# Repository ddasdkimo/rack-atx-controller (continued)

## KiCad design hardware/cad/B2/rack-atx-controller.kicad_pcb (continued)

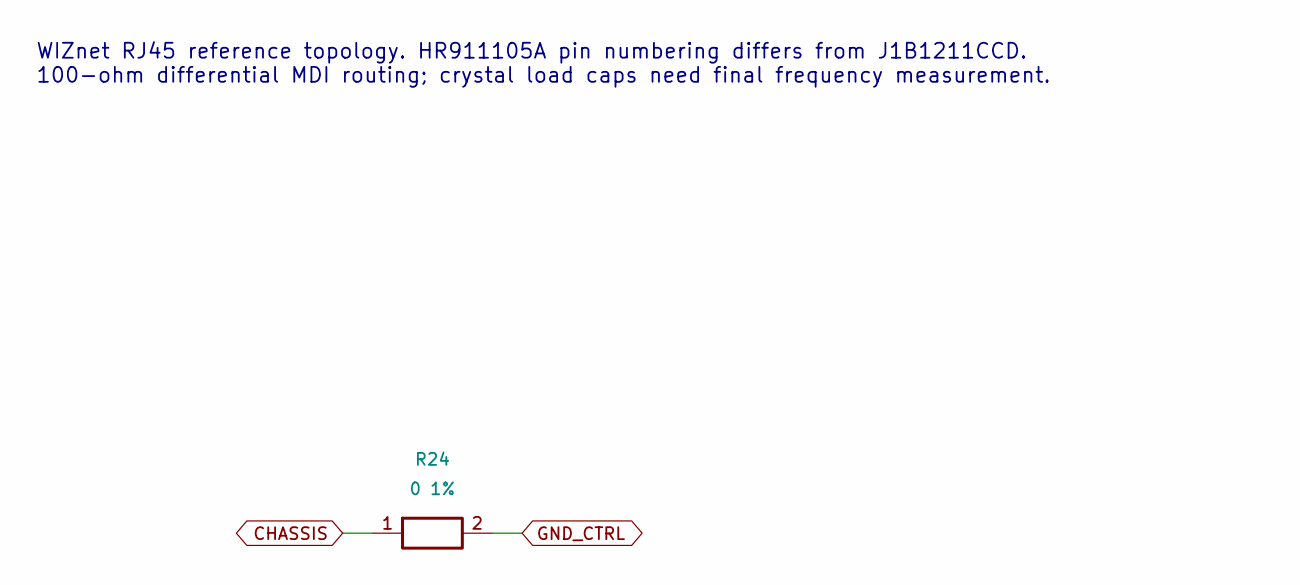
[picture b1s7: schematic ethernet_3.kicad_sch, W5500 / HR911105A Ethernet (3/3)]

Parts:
R24: 0 1%; R_0603_1608Metric; MPN 0603WAF0000T5E; LCSC C21189

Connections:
CHASSIS: R24.1; also elsewhere on the board
GND_CTRL: R24.2; also elsewhere on the board

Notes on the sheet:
WIZnet RJ45 reference topology. HR911105A pin numbering differs from J1B1211CCD. 100-ohm differential MDI routing; crystal load caps need final frequency measurement.

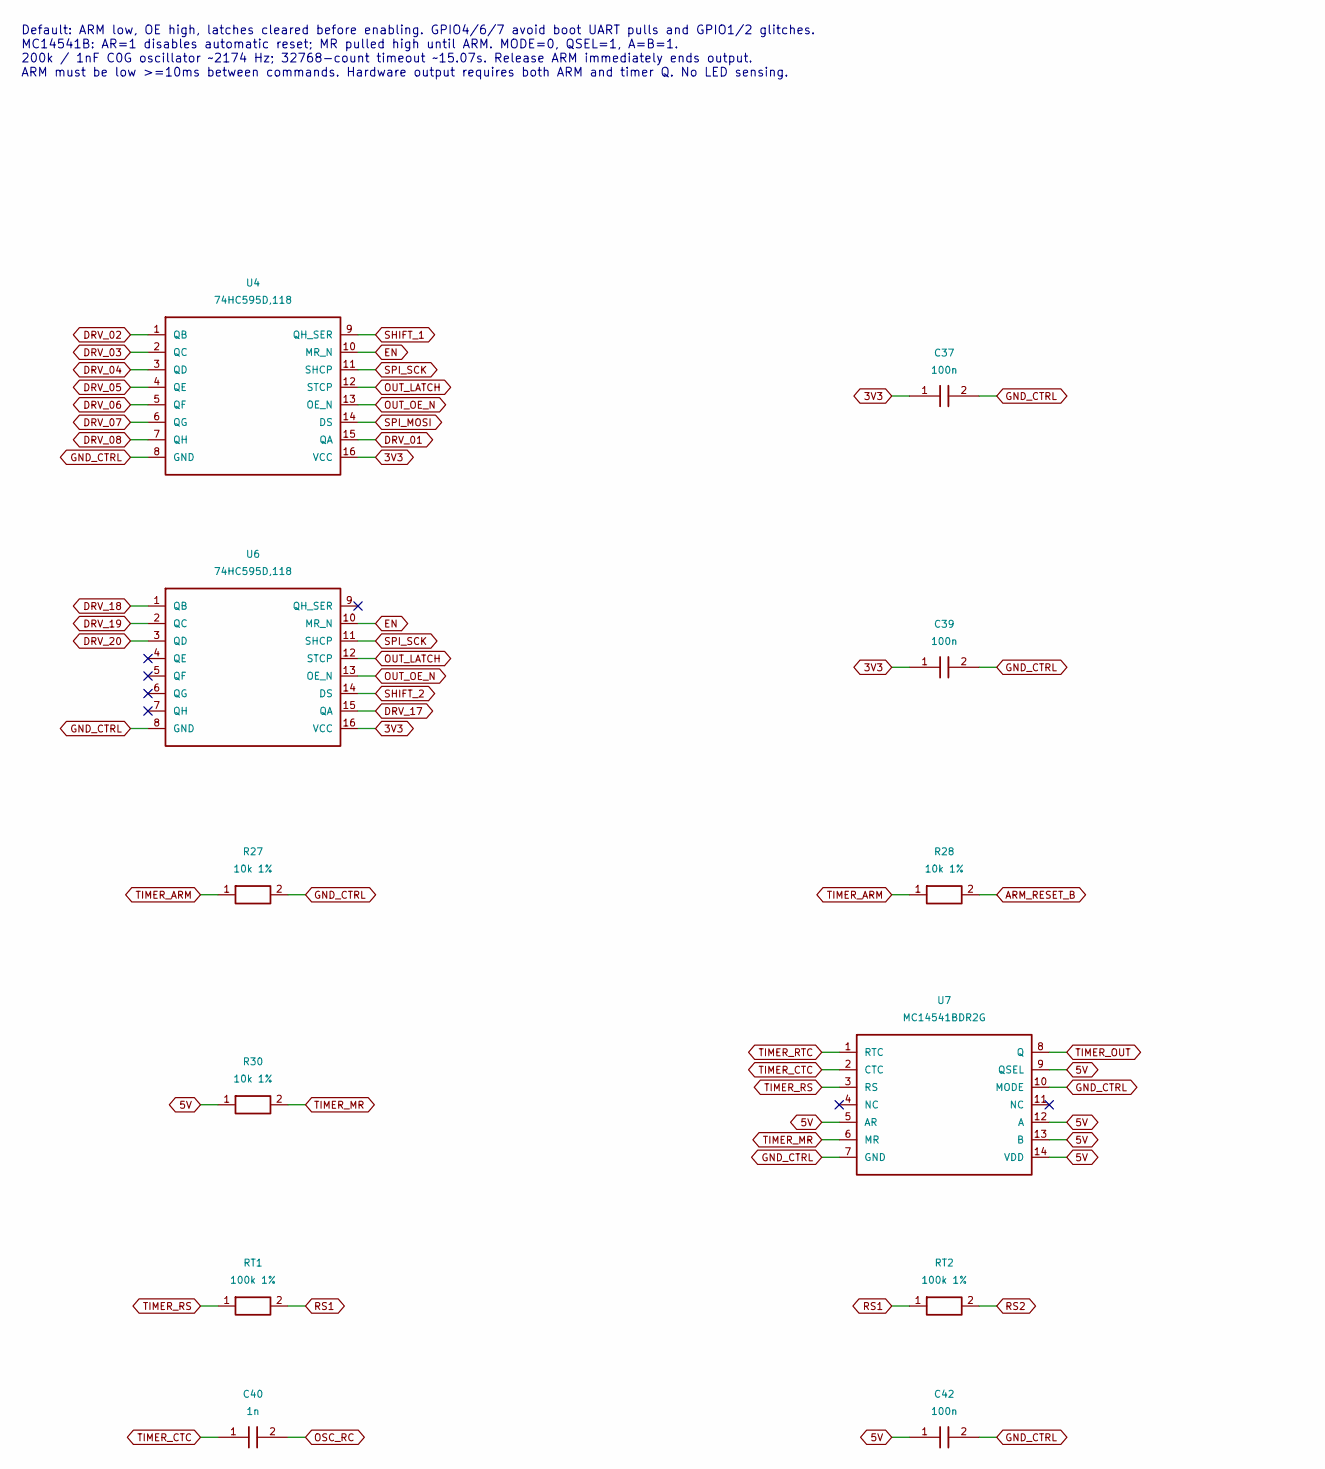
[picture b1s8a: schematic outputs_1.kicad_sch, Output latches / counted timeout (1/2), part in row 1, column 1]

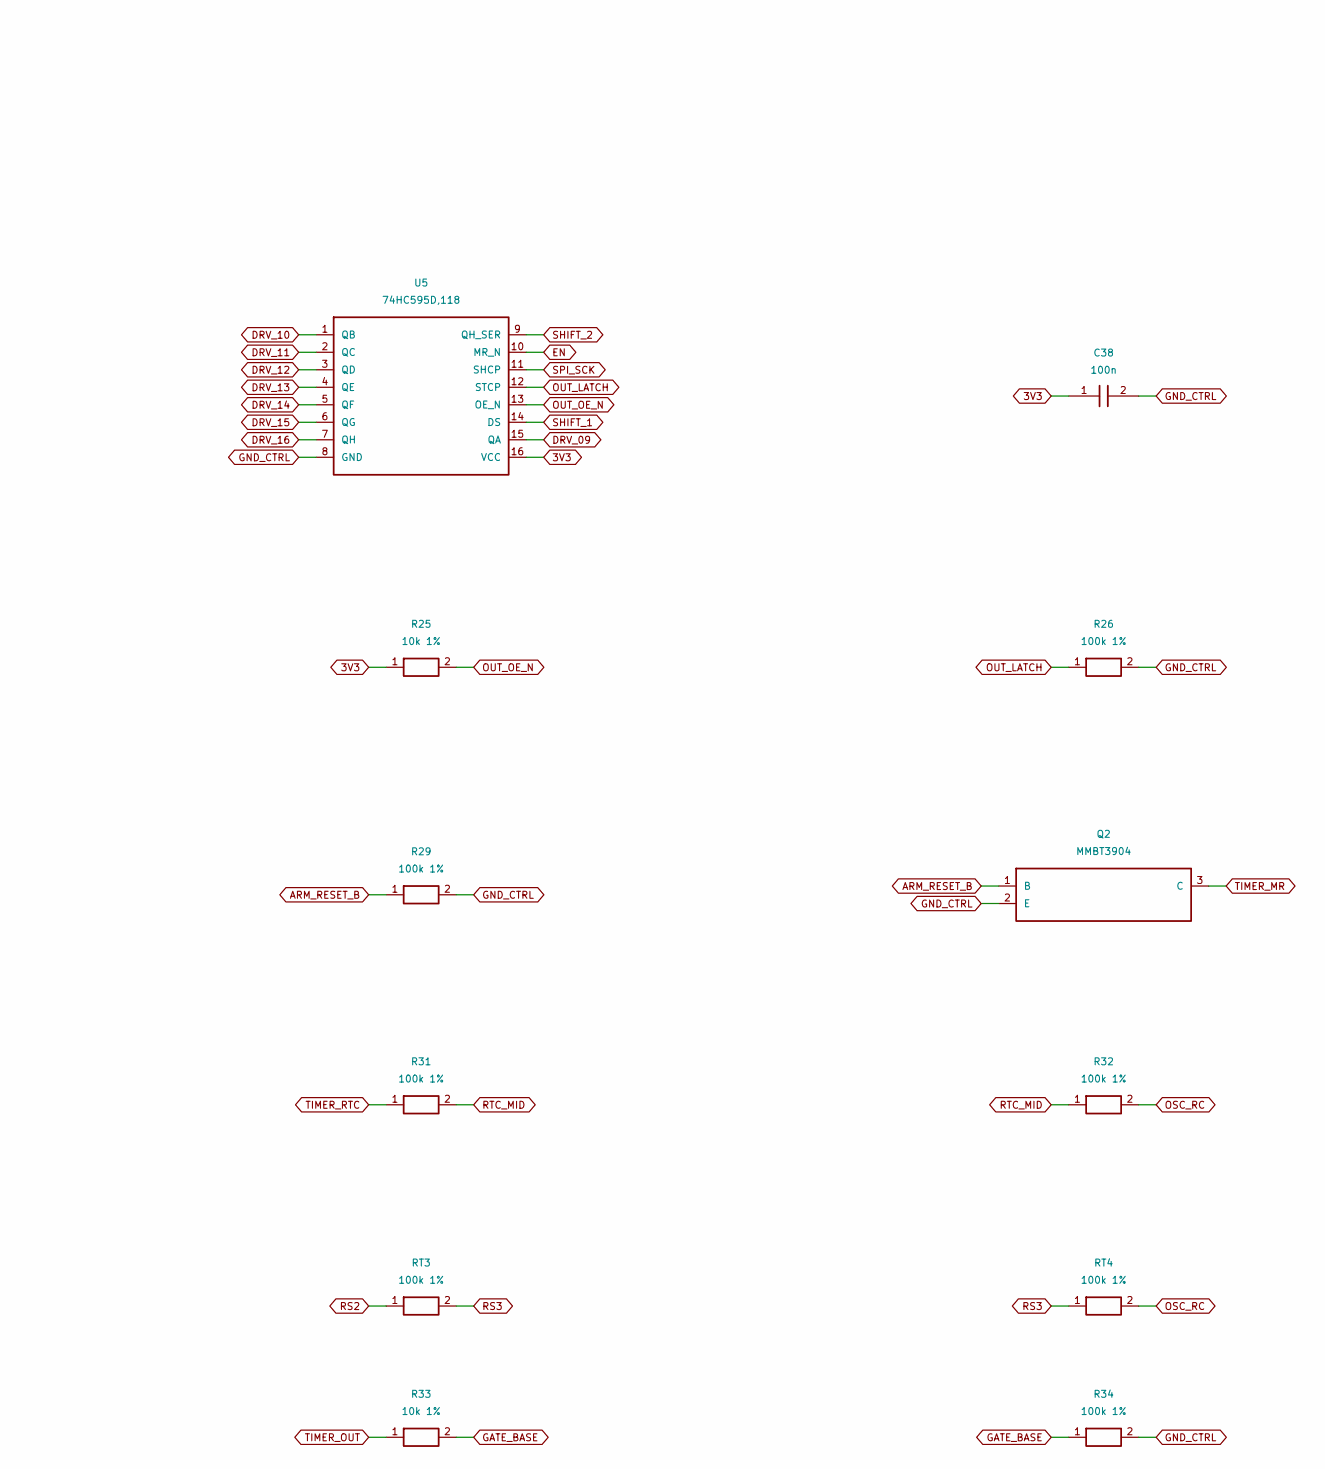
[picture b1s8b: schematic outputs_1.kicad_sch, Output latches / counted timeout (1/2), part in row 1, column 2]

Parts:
C37, C38, C39, C42: 100n; C_0603_1608Metric; MPN CC0603KRX7R9BB104; LCSC C14663
C40: 1n; C_0603_1608Metric; MPN CL10C102JB8NNNC; LCSC C163508
Q2: MMBT3904; SOT-23; MPN MMBT3904(RANGE:100-300); LCSC C20526
R25, R27, R28, R30, R33: 10k 1%; R_0603_1608Metric; MPN 0603WAF1002T5E; LCSC C25804
R26, R29, R31, R32, R34: 100k 1%; R_0603_1608Metric; MPN 0603WAF1003T5E; LCSC C25803
RT1, RT2, RT3, RT4: 100k 1%; R_0603_1608Metric; MPN 0603WAF1003T5E; LCSC C25803
U4, U5, U6: 74HC595D,118; SOIC-16_3.9x9.9mm_P1.27mm; MPN 74HC595D,118; LCSC C5947
U7: MC14541BDR2G; SOIC-14_3.9x8.7mm_P1.27mm; MPN MC14541BDR2G; LCSC C7292

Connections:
3V3: C37.1, C38.1, C39.1, R25.1, U4.16 (VCC), U5.16 (VCC), U6.16 (VCC); also elsewhere on the board
5V: C42.1, R30.1, U7.5 (AR), U7.9 (QSEL), U7.12 (A), U7.13 (B), U7.14 (VDD); also elsewhere on the board
ARM_RESET_B: Q2.1 (B), R28.2, R29.1
DRV_01: U4.15 (QA); also elsewhere on the board
DRV_02: U4.1 (QB); also elsewhere on the board
DRV_03: U4.2 (QC); also elsewhere on the board
DRV_04: U4.3 (QD); also elsewhere on the board
DRV_05: U4.4 (QE); also elsewhere on the board
DRV_06: U4.5 (QF); also elsewhere on the board
DRV_07: U4.6 (QG); also elsewhere on the board
DRV_08: U4.7 (QH); also elsewhere on the board
DRV_09: U5.15 (QA); also elsewhere on the board
DRV_10: U5.1 (QB); also elsewhere on the board
DRV_11: U5.2 (QC); also elsewhere on the board
DRV_12: U5.3 (QD); also elsewhere on the board
DRV_13: U5.4 (QE); also elsewhere on the board
DRV_14: U5.5 (QF); also elsewhere on the board
DRV_15: U5.6 (QG); also elsewhere on the board
DRV_16: U5.7 (QH); also elsewhere on the board
DRV_17: U6.15 (QA); also elsewhere on the board
DRV_18: U6.1 (QB); also elsewhere on the board
DRV_19: U6.2 (QC); also elsewhere on the board
DRV_20: U6.3 (QD); also elsewhere on the board
EN: U4.10 (MR_N), U5.10 (MR_N), U6.10 (MR_N); also elsewhere on the board
GATE_BASE: R33.2, R34.1; also elsewhere on the board
GND_CTRL: C37.2, C38.2, C39.2, C42.2, Q2.2 (E), R26.2, R27.2, R29.2, R34.2, U4.8 (GND), U5.8 (GND), U6.8 (GND), U7.7 (GND), U7.10 (MODE); also elsewhere on the board
OSC_RC: C40.2, R32.2, RT4.2
OUT_LATCH: R26.1, U4.12 (STCP), U5.12 (STCP), U6.12 (STCP); also elsewhere on the board
OUT_OE_N: R25.2, U4.13 (OE_N), U5.13 (OE_N), U6.13 (OE_N); also elsewhere on the board
RS1: RT1.2, RT2.1
RS2: RT2.2, RT3.1
RS3: RT3.2, RT4.1
RTC_MID: R31.2, R32.1
SHIFT_1: U4.9 (QH_SER), U5.14 (DS)
SHIFT_2: U5.9 (QH_SER), U6.14 (DS)
SPI_MOSI: U4.14 (DS); also elsewhere on the board
SPI_SCK: U4.11 (SHCP), U5.11 (SHCP), U6.11 (SHCP); also elsewhere on the board
TIMER_ARM: R27.1, R28.1; also elsewhere on the board
TIMER_CTC: C40.1, U7.2 (CTC)
TIMER_MR: Q2.3 (C), R30.2, U7.6 (MR)
TIMER_OUT: R33.1, U7.8 (Q)
TIMER_RS: RT1.1, U7.3 (RS)
TIMER_RTC: R31.1, U7.1 (RTC)

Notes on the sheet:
Default: ARM low, OE high, latches cleared before enabling. GPIO4/6/7 avoid boot UART pulls and GPIO1/2 glitches. MC14541B: AR=1 disables automatic reset; MR pulled high until ARM. MODE=0, QSEL=1, A=B=1. 200k / 1nF C0G oscillator ~2174 Hz; 32768-count timeout ~15.07s. Release ARM immediately ends o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

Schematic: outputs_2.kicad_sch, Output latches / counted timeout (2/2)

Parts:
Q3, Q200: MMBT3904; SOT-23; MPN MMBT3904(RANGE:100-300); LCSC C20526
Q4: AO3401A; SOT-23; MPN AO3401A; LCSC C15127
R35, R36, R37: 10k 1%; R_0603_1608Metric; MPN 0603WAF1002T5E; LCSC C25804
R38: 100k 1%; R_0603_1608Metric; MPN 0603WAF1003T5E; LCSC C25803

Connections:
5V: Q4.2 (S), R35.2; also elsewhere on the board
ARM_GATE_B: Q200.1 (B), R37.2, R38.1
ARM_SINK: Q3.2 (E), Q200.3 (C)
GATE_BASE: Q3.1 (B); also elsewhere on the board
GND_CTRL: Q200.2 (E), R36.2, R38.2; also elsewhere on the board
PHOTO_5V: Q4.3 (D), R36.1; also elsewhere on the board
PHOTO_GATE: Q3.3 (C), Q4.1 (G), R35.1
TIMER_ARM: R37.1; also elsewhere on the board

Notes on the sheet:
Default: ARM low, OE high, latches cleared before enabling. GPIO4/6/7 avoid boot UART pulls and GPIO1/2 glitches. MC14541B: AR=1 disables automatic reset; MR pulled high until ARM. MODE=0, QSEL=1, A=B=1. 200k / 1nF C0G oscillator ~2174 Hz; 32768-count timeout ~15.07s. Release ARM immediately ends o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

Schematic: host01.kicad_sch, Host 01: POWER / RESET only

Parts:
D2, D3: PESD5V0S2BT; SOT-23; MPN PESD5V0S2BT; LCSC C2841440
D101, D102: KT-0603R / RED; LED_0603_1608Metric_CathodeSilk; MPN KT-0603R; LCSC C2286
J01: S10B-PHDSS(LF)(SN); JST_PHD_S10B-PHDSS_2x05_P2.00mm_Horizontal; MPN S10B-PHDSS(LF)(SN); LCSC C161672
Q5, Q6: MMBT3904; SOT-23; MPN MMBT3904(RANGE:100-300); LCSC C20526
R39, R43, R301, R302: 1.5k 1%; R_0603_1608Metric; MPN 0603WAF1501T5E; LCSC C22843
R40, R44: 100k 1%; R_0603_1608Metric; MPN 0603WAF1003T5E; LCSC C25803
R41, R42, R45, R46: 220 1%; R_0603_1608Metric; MPN 0603WAF2200T5E; LCSC C22962
U8, U9: TLP3122A(TPL,E; TLP3122A_11-4M1S; MPN TLP3122A(TPL,E; LCSC C4153843

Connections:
CTRL_H01_PWR_A: R42.2, U8.1 (A)
CTRL_H01_PWR_B: Q5.1 (B), R39.2, R40.1
CTRL_H01_PWR_IND_A: D101.2 (A), R301.2
CTRL_H01_PWR_K: D101.1 (K), Q5.3 (C), U8.3 (K)
CTRL_H01_PWR_R: R41.2, R42.1
CTRL_H01_RST_A: R46.2, U9.1 (A)
CTRL_H01_RST_B: Q6.1 (B), R43.2, R44.1
CTRL_H01_RST_IND_A: D102.2 (A), R302.2
CTRL_H01_RST_K: D102.1 (K), Q6.3 (C), U9.3 (K)
CTRL_H01_RST_R: R45.2, R46.1
DRV_01: R39.1; also elsewhere on the board
DRV_02: R43.1; also elsewhere on the board
GND_CTRL: Q5.2 (E), Q6.2 (E), R40.2, R44.2; also elsewhere on the board
H01_GND: D2.3 (GND), D3.3 (GND), J01.9 (HOST_REF)
H01_PWR_A: D2.1 (IO1), J01.1 (PWR_A), U8.4 (OUT)
H01_PWR_B: D2.2 (IO2), J01.2 (PWR_B), U8.6 (OUT)
H01_RST_A: D3.1 (IO1), J01.3 (RST_A), U9.4 (OUT)
H01_RST_B: D3.2 (IO2), J01.4 (RST_B), U9.6 (OUT)
PHOTO_5V: R41.1, R45.1, R301.1, R302.1; also elsewhere on the board

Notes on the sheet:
Two isolated normally-open contacts parallel the original case buttons. No host LED sensing or isolated supply. Pin 9 remains this host reference for button ESD protection ONLY. Do not join host references to controller ground or to one another. Pins 5..8 and 10 are NC. Use verified motherboard sig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

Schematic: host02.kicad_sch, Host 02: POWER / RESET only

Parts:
D4, D5: PESD5V0S2BT; SOT-23; MPN PESD5V0S2BT; LCSC C2841440
D103, D104: KT-0603R / RED; LED_0603_1608Metric_CathodeSilk; MPN KT-0603R; LCSC C2286
J02: S10B-PHDSS(LF)(SN); JST_PHD_S10B-PHDSS_2x05_P2.00mm_Horizontal; MPN S10B-PHDSS(LF)(SN); LCSC C161672
Q7, Q8: MMBT3904; SOT-23; MPN MMBT3904(RANGE:100-300); LCSC C20526
R47, R51, R303, R304: 1.5k 1%; R_0603_1608Metric; MPN 0603WAF1501T5E; LCSC C22843
R48, R52: 100k 1%; R_0603_1608Metric; MPN 0603WAF1003T5E; LCSC C25803
R49, R50, R53, R54: 220 1%; R_0603_1608Metric; MPN 0603WAF2200T5E; LCSC C22962
U10, U11: TLP3122A(TPL,E; TLP3122A_11-4M1S; MPN TLP3122A(TPL,E; LCSC C4153843

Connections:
CTRL_H02_PWR_A: R50.2, U10.1 (A)
CTRL_H02_PWR_B: Q7.1 (B), R47.2, R48.1
CTRL_H02_PWR_IND_A: D103.2 (A), R303.2
CTRL_H02_PWR_K: D103.1 (K), Q7.3 (C), U10.3 (K)
CTRL_H02_PWR_R: R49.2, R50.1
CTRL_H02_RST_A: R54.2, U11.1 (A)
CTRL_H02_RST_B: Q8.1 (B), R51.2, R52.1
CTRL_H02_RST_IND_A: D104.2 (A), R304.2
CTRL_H02_RST_K: D104.1 (K), Q8.3 (C), U11.3 (K)
CTRL_H02_RST_R: R53.2, R54.1
DRV_03: R47.1; also elsewhere on the board
DRV_04: R51.1; also elsewhere on the board
GND_CTRL: Q7.2 (E), Q8.2 (E), R48.2, R52.2; also elsewhere on the board
H02_GND: D4.3 (GND), D5.3 (GND), J02.9 (HOST_REF)
H02_PWR_A: D4.1 (IO1), J02.1 (PWR_A), U10.4 (OUT)
H02_PWR_B: D4.2 (IO2), J02.2 (PWR_B), U10.6 (OUT)
H02_RST_A: D5.1 (IO1), J02.3 (RST_A), U11.4 (OUT)
H02_RST_B: D5.2 (IO2), J02.4 (RST_B), U11.6 (OUT)
PHOTO_5V: R49.1, R53.1, R303.1, R304.1; also elsewhere on the board

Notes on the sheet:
Two isolated normally-open contacts parallel the original case buttons. No host LED sensing or isolated supply. Pin 9 remains this host reference for button ESD protection ONLY. Do not join host references to controller ground or to one another. Pins 5..8 and 10 are NC. Use verified motherboard sig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

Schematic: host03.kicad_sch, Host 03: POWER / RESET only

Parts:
D6, D7: PESD5V0S2BT; SOT-23; MPN PESD5V0S2BT; LCSC C2841440
D105, D106: KT-0603R / RED; LED_0603_1608Metric_CathodeSilk; MPN KT-0603R; LCSC C2286
J03: S10B-PHDSS(LF)(SN); JST_PHD_S10B-PHDSS_2x05_P2.00mm_Horizontal; MPN S10B-PHDSS(LF)(SN); LCSC C161672
Q9, Q10: MMBT3904; SOT-23; MPN MMBT3904(RANGE:100-300); LCSC C20526
R55, R59, R305, R306: 1.5k 1%; R_0603_1608Metric; MPN 0603WAF1501T5E; LCSC C22843
R56, R60: 100k 1%; R_0603_1608Metric; MPN 0603WAF1003T5E; LCSC C25803
R57, R58, R61, R62: 220 1%; R_0603_1608Metric; MPN 0603WAF2200T5E; LCSC C22962
U12, U13: TLP3122A(TPL,E; TLP3122A_11-4M1S; MPN TLP3122A(TPL,E; LCSC C4153843

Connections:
CTRL_H03_PWR_A: R58.2, U12.1 (A)
CTRL_H03_PWR_B: Q9.1 (B), R55.2, R56.1
CTRL_H03_PWR_IND_A: D105.2 (A), R305.2
CTRL_H03_PWR_K: D105.1 (K), Q9.3 (C), U12.3 (K)
CTRL_H03_PWR_R: R57.2, R58.1
CTRL_H03_RST_A: R62.2, U13.1 (A)
CTRL_H03_RST_B: Q10.1 (B), R59.2, R60.1
CTRL_H03_RST_IND_A: D106.2 (A), R306.2
CTRL_H03_RST_K: D106.1 (K), Q10.3 (C), U13.3 (K)
CTRL_H03_RST_R: R61.2, R62.1
DRV_05: R55.1; also elsewhere on the board
DRV_06: R59.1; also elsewhere on the board
GND_CTRL: Q9.2 (E), Q10.2 (E), R56.2, R60.2; also elsewhere on the board
H03_GND: D6.3 (GND), D7.3 (GND), J03.9 (HOST_REF)
H03_PWR_A: D6.1 (IO1), J03.1 (PWR_A), U12.4 (OUT)
H03_PWR_B: D6.2 (IO2), J03.2 (PWR_B), U12.6 (OUT)
H03_RST_A: D7.1 (IO1), J03.3 (RST_A), U13.4 (OUT)
H03_RST_B: D7.2 (IO2), J03.4 (RST_B), U13.6 (OUT)
PHOTO_5V: R57.1, R61.1, R305.1, R306.1; also elsewhere on the board

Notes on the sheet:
Two isolated normally-open contacts parallel the original case buttons. No host LED sensing or isolated supply. Pin 9 remains this host reference for button ESD protection ONLY. Do not join host references to controller ground or to one another. Pins 5..8 and 10 are NC. Use verified motherboard sig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

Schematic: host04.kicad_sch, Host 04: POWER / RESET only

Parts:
D8, D9: PESD5V0S2BT; SOT-23; MPN PESD5V0S2BT; LCSC C2841440
D107, D108: KT-0603R / RED; LED_0603_1608Metric_CathodeSilk; MPN KT-0603R; LCSC C2286
J04: S10B-PHDSS(LF)(SN); JST_PHD_S10B-PHDSS_2x05_P2.00mm_Horizontal; MPN S10B-PHDSS(LF)(SN); LCSC C161672
Q11, Q12: MMBT3904; SOT-23; MPN MMBT3904(RANGE:100-300); LCSC C20526
R63, R67, R307, R308: 1.5k 1%; R_0603_1608Metric; MPN 0603WAF1501T5E; LCSC C22843
R64, R68: 100k 1%; R_0603_1608Metric; MPN 0603WAF1003T5E; LCSC C25803
R65, R66, R69, R70: 220 1%; R_0603_1608Metric; MPN 0603WAF2200T5E; LCSC C22962
U14, U15: TLP3122A(TPL,E; TLP3122A_11-4M1S; MPN TLP3122A(TPL,E; LCSC C4153843

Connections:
CTRL_H04_PWR_A: R66.2, U14.1 (A)
CTRL_H04_PWR_B: Q11.1 (B), R63.2, R64.1
CTRL_H04_PWR_IND_A: D107.2 (A), R307.2
CTRL_H04_PWR_K: D107.1 (K), Q11.3 (C), U14.3 (K)
CTRL_H04_PWR_R: R65.2, R66.1
CTRL_H04_RST_A: R70.2, U15.1 (A)
CTRL_H04_RST_B: Q12.1 (B), R67.2, R68.1
CTRL_H04_RST_IND_A: D108.2 (A), R308.2
CTRL_H04_RST_K: D108.1 (K), Q12.3 (C), U15.3 (K)
CTRL_H04_RST_R: R69.2, R70.1
DRV_07: R63.1; also elsewhere on the board
DRV_08: R67.1; also elsewhere on the board
GND_CTRL: Q11.2 (E), Q12.2 (E), R64.2, R68.2; also elsewhere on the board
H04_GND: D8.3 (GND), D9.3 (GND), J04.9 (HOST_REF)
H04_PWR_A: D8.1 (IO1), J04.1 (PWR_A), U14.4 (OUT)
H04_PWR_B: D8.2 (IO2), J04.2 (PWR_B), U14.6 (OUT)
H04_RST_A: D9.1 (IO1), J04.3 (RST_A), U15.4 (OUT)
H04_RST_B: D9.2 (IO2), J04.4 (RST_B), U15.6 (OUT)
PHOTO_5V: R65.1, R69.1, R307.1, R308.1; also elsewhere on the board

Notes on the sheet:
Two isolated normally-open contacts parallel the original case buttons. No host LED sensing or isolated supply. Pin 9 remains this host reference for button ESD protection ONLY. Do not join host references to controller ground or to one another. Pins 5..8 and 10 are NC. Use verified motherboard sig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

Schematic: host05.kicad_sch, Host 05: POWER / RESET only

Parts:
D10, D11: PESD5V0S2BT; SOT-23; MPN PESD5V0S2BT; LCSC C2841440
D109, D110: KT-0603R / RED; LED_0603_1608Metric_CathodeSilk; MPN KT-0603R; LCSC C2286
J05: S10B-PHDSS(LF)(SN); JST_PHD_S10B-PHDSS_2x05_P2.00mm_Horizontal; MPN S10B-PHDSS(LF)(SN); LCSC C161672
Q13, Q14: MMBT3904; SOT-23; MPN MMBT3904(RANGE:100-300); LCSC C20526
R71, R75, R309, R310: 1.5k 1%; R_0603_1608Metric; MPN 0603WAF1501T5E; LCSC C22843
R72, R76: 100k 1%; R_0603_1608Metric; MPN 0603WAF1003T5E; LCSC C25803
R73, R74, R77, R78: 220 1%; R_0603_1608Metric; MPN 0603WAF2200T5E; LCSC C22962
U16, U17: TLP3122A(TPL,E; TLP3122A_11-4M1S; MPN TLP3122A(TPL,E; LCSC C4153843

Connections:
CTRL_H05_PWR_A: R74.2, U16.1 (A)
CTRL_H05_PWR_B: Q13.1 (B), R71.2, R72.1
CTRL_H05_PWR_IND_A: D109.2 (A), R309.2
CTRL_H05_PWR_K: D109.1 (K), Q13.3 (C), U16.3 (K)
CTRL_H05_PWR_R: R73.2, R74.1
CTRL_H05_RST_A: R78.2, U17.1 (A)
CTRL_H05_RST_B: Q14.1 (B), R75.2, R76.1
CTRL_H05_RST_IND_A: D110.2 (A), R310.2
CTRL_H05_RST_K: D110.1 (K), Q14.3 (C), U17.3 (K)
CTRL_H05_RST_R: R77.2, R78.1
DRV_09: R71.1; also elsewhere on the board
DRV_10: R75.1; also elsewhere on the board
GND_CTRL: Q13.2 (E), Q14.2 (E), R72.2, R76.2; also elsewhere on the board
H05_GND: D10.3 (GND), D11.3 (GND), J05.9 (HOST_REF)
H05_PWR_A: D10.1 (IO1), J05.1 (PWR_A), U16.4 (OUT)
H05_PWR_B: D10.2 (IO2), J05.2 (PWR_B), U16.6 (OUT)
H05_RST_A: D11.1 (IO1), J05.3 (RST_A), U17.4 (OUT)
H05_RST_B: D11.2 (IO2), J05.4 (RST_B), U17.6 (OUT)
PHOTO_5V: R73.1, R77.1, R309.1, R310.1; also elsewhere on the board

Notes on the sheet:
Two isolated normally-open contacts parallel the original case buttons. No host LED sensing or isolated supply. Pin 9 remains this host reference for button ESD protection ONLY. Do not join host references to controller ground or to one another. Pins 5..8 and 10 are NC. Use verified motherboard sig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

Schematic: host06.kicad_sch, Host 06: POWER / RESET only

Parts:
D12, D13: PESD5V0S2BT; SOT-23; MPN PESD5V0S2BT; LCSC C2841440
D111, D112: KT-0603R / RED; LED_0603_1608Metric_CathodeSilk; MPN KT-0603R; LCSC C2286
J06: S10B-PHDSS(LF)(SN); JST_PHD_S10B-PHDSS_2x05_P2.00mm_Horizontal; MPN S10B-PHDSS(LF)(SN); LCSC C161672
Q15, Q16: MMBT3904; SOT-23; MPN MMBT3904(RANGE:100-300); LCSC C20526
R79, R83, R311, R312: 1.5k 1%; R_0603_1608Metric; MPN 0603WAF1501T5E; LCSC C22843
R80, R84: 100k 1%; R_0603_1608Metric; MPN 0603WAF1003T5E; LCSC C25803
R81, R82, R85, R86: 220 1%; R_0603_1608Metric; MPN 0603WAF2200T5E; LCSC C22962
U18, U19: TLP3122A(TPL,E; TLP3122A_11-4M1S; MPN TLP3122A(TPL,E; LCSC C4153843

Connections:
CTRL_H06_PWR_A: R82.2, U18.1 (A)
CTRL_H06_PWR_B: Q15.1 (B), R79.2, R80.1
CTRL_H06_PWR_IND_A: D111.2 (A), R311.2
CTRL_H06_PWR_K: D111.1 (K), Q15.3 (C), U18.3 (K)
CTRL_H06_PWR_R: R81.2, R82.1
CTRL_H06_RST_A: R86.2, U19.1 (A)
CTRL_H06_RST_B: Q16.1 (B), R83.2, R84.1
CTRL_H06_RST_IND_A: D112.2 (A), R312.2
CTRL_H06_RST_K: D112.1 (K), Q16.3 (C), U19.3 (K)
CTRL_H06_RST_R: R85.2, R86.1
DRV_11: R79.1; also elsewhere on the board
DRV_12: R83.1; also elsewhere on the board
GND_CTRL: Q15.2 (E), Q16.2 (E), R80.2, R84.2; also elsewhere on the board
H06_GND: D12.3 (GND), D13.3 (GND), J06.9 (HOST_REF)
H06_PWR_A: D12.1 (IO1), J06.1 (PWR_A), U18.4 (OUT)
H06_PWR_B: D12.2 (IO2), J06.2 (PWR_B), U18.6 (OUT)
H06_RST_A: D13.1 (IO1), J06.3 (RST_A), U19.4 (OUT)
H06_RST_B: D13.2 (IO2), J06.4 (RST_B), U19.6 (OUT)
PHOTO_5V: R81.1, R85.1, R311.1, R312.1; also elsewhere on the board

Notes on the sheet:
Two isolated normally-open contacts parallel the original case buttons. No host LED sensing or isolated supply. Pin 9 remains this host reference for button ESD protection ONLY. Do not join host references to controller ground or to one another. Pins 5..8 and 10 are NC. Use verified motherboard sig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

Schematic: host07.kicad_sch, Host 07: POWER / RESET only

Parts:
D14, D15: PESD5V0S2BT; SOT-23; MPN PESD5V0S2BT; LCSC C2841440
D113, D114: KT-0603R / RED; LED_0603_1608Metric_CathodeSilk; MPN KT-0603R; LCSC C2286
J07: S10B-PHDSS(LF)(SN); JST_PHD_S10B-PHDSS_2x05_P2.00mm_Horizontal; MPN S10B-PHDSS(LF)(SN); LCSC C161672
Q17, Q18: MMBT3904; SOT-23; MPN MMBT3904(RANGE:100-300); LCSC C20526
R87, R91, R313, R314: 1.5k 1%; R_0603_1608Metric; MPN 0603WAF1501T5E; LCSC C22843
R88, R92: 100k 1%; R_0603_1608Metric; MPN 0603WAF1003T5E; LCSC C25803
R89, R90, R93, R94: 220 1%; R_0603_1608Metric; MPN 0603WAF2200T5E; LCSC C22962
U20, U21: TLP3122A(TPL,E; TLP3122A_11-4M1S; MPN TLP3122A(TPL,E; LCSC C4153843

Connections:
CTRL_H07_PWR_A: R90.2, U20.1 (A)
CTRL_H07_PWR_B: Q17.1 (B), R87.2, R88.1
CTRL_H07_PWR_IND_A: D113.2 (A), R313.2
CTRL_H07_PWR_K: D113.1 (K), Q17.3 (C), U20.3 (K)
CTRL_H07_PWR_R: R89.2, R90.1
CTRL_H07_RST_A: R94.2, U21.1 (A)
CTRL_H07_RST_B: Q18.1 (B), R91.2, R92.1
CTRL_H07_RST_IND_A: D114.2 (A), R314.2
CTRL_H07_RST_K: D114.1 (K), Q18.3 (C), U21.3 (K)
CTRL_H07_RST_R: R93.2, R94.1
DRV_13: R87.1; also elsewhere on the board
DRV_14: R91.1; also elsewhere on the board
GND_CTRL: Q17.2 (E), Q18.2 (E), R88.2, R92.2; also elsewhere on the board
H07_GND: D14.3 (GND), D15.3 (GND), J07.9 (HOST_REF)
H07_PWR_A: D14.1 (IO1), J07.1 (PWR_A), U20.4 (OUT)
H07_PWR_B: D14.2 (IO2), J07.2 (PWR_B), U20.6 (OUT)
H07_RST_A: D15.1 (IO1), J07.3 (RST_A), U21.4 (OUT)
H07_RST_B: D15.2 (IO2), J07.4 (RST_B), U21.6 (OUT)
PHOTO_5V: R89.1, R93.1, R313.1, R314.1; also elsewhere on the board

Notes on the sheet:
Two isolated normally-open contacts parallel the original case buttons. No host LED sensing or isolated supply. Pin 9 remains this host reference for button ESD protection ONLY. Do not join host references to controller ground or to one another. Pins 5..8 and 10 are NC. Use verified motherboard sig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

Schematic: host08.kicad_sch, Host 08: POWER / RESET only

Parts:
D16, D17: PESD5V0S2BT; SOT-23; MPN PESD5V0S2BT; LCSC C2841440
D115, D116: KT-0603R / RED; LED_0603_1608Metric_CathodeSilk; MPN KT-0603R; LCSC C2286
J08: S10B-PHDSS(LF)(SN); JST_PHD_S10B-PHDSS_2x05_P2.00mm_Horizontal; MPN S10B-PHDSS(LF)(SN); LCSC C161672
Q19, Q20: MMBT3904; SOT-23; MPN MMBT3904(RANGE:100-300); LCSC C20526
R95, R99, R315, R316: 1.5k 1%; R_0603_1608Metric; MPN 0603WAF1501T5E; LCSC C22843
R96, R100: 100k 1%; R_0603_1608Metric; MPN 0603WAF1003T5E; LCSC C25803
R97, R98, R101, R102: 220 1%; R_0603_1608Metric; MPN 0603WAF2200T5E; LCSC C22962
U22, U23: TLP3122A(TPL,E; TLP3122A_11-4M1S; MPN TLP3122A(TPL,E; LCSC C4153843

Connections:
CTRL_H08_PWR_A: R98.2, U22.1 (A)
CTRL_H08_PWR_B: Q19.1 (B), R95.2, R96.1
CTRL_H08_PWR_IND_A: D115.2 (A), R315.2
CTRL_H08_PWR_K: D115.1 (K), Q19.3 (C), U22.3 (K)
CTRL_H08_PWR_R: R97.2, R98.1
CTRL_H08_RST_A: R102.2, U23.1 (A)
CTRL_H08_RST_B: Q20.1 (B), R99.2, R100.1
CTRL_H08_RST_IND_A: D116.2 (A), R316.2
CTRL_H08_RST_K: D116.1 (K), Q20.3 (C), U23.3 (K)
CTRL_H08_RST_R: R101.2, R102.1
DRV_15: R95.1; also elsewhere on the board
DRV_16: R99.1; also elsewhere on the board
GND_CTRL: Q19.2 (E), Q20.2 (E), R96.2, R100.2; also elsewhere on the board
H08_GND: D16.3 (GND), D17.3 (GND), J08.9 (HOST_REF)
H08_PWR_A: D16.1 (IO1), J08.1 (PWR_A), U22.4 (OUT)
H08_PWR_B: D16.2 (IO2), J08.2 (PWR_B), U22.6 (OUT)
H08_RST_A: D17.1 (IO1), J08.3 (RST_A), U23.4 (OUT)
H08_RST_B: D17.2 (IO2), J08.4 (RST_B), U23.6 (OUT)
PHOTO_5V: R97.1, R101.1, R315.1, R316.1; also elsewhere on the board

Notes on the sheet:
Two isolated normally-open contacts parallel the original case buttons. No host LED sensing or isolated supply. Pin 9 remains this host reference for button ESD protection ONLY. Do not join host references to controller ground or to one another. Pins 5..8 and 10 are NC. Use verified motherboard sig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

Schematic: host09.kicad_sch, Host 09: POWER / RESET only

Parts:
D18, D19: PESD5V0S2BT; SOT-23; MPN PESD5V0S2BT; LCSC C2841440
D117, D118: KT-0603R / RED; LED_0603_1608Metric_CathodeSilk; MPN KT-0603R; LCSC C2286
J09: S10B-PHDSS(LF)(SN); JST_PHD_S10B-PHDSS_2x05_P2.00mm_Horizontal; MPN S10B-PHDSS(LF)(SN); LCSC C161672
Q21, Q22: MMBT3904; SOT-23; MPN MMBT3904(RANGE:100-300); LCSC C20526
R103, R107, R317, R318: 1.5k 1%; R_0603_1608Metric; MPN 0603WAF1501T5E; LCSC C22843
R104, R108: 100k 1%; R_0603_1608Metric; MPN 0603WAF1003T5E; LCSC C25803
R105, R106, R109, R110: 220 1%; R_0603_1608Metric; MPN 0603WAF2200T5E; LCSC C22962
U24, U25: TLP3122A(TPL,E; TLP3122A_11-4M1S; MPN TLP3122A(TPL,E; LCSC C4153843

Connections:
CTRL_H09_PWR_A: R106.2, U24.1 (A)
CTRL_H09_PWR_B: Q21.1 (B), R103.2, R104.1
CTRL_H09_PWR_IND_A: D117.2 (A), R317.2
CTRL_H09_PWR_K: D117.1 (K), Q21.3 (C), U24.3 (K)
CTRL_H09_PWR_R: R105.2, R106.1
CTRL_H09_RST_A: R110.2, U25.1 (A)
CTRL_H09_RST_B: Q22.1 (B), R107.2, R108.1
CTRL_H09_RST_IND_A: D118.2 (A), R318.2
CTRL_H09_RST_K: D118.1 (K), Q22.3 (C), U25.3 (K)
CTRL_H09_RST_R: R109.2, R110.1
DRV_17: R103.1; also elsewhere on the board
DRV_18: R107.1; also elsewhere on the board
GND_CTRL: Q21.2 (E), Q22.2 (E), R104.2, R108.2; also elsewhere on the board
H09_GND: D18.3 (GND), D19.3 (GND), J09.9 (HOST_REF)
H09_PWR_A: D18.1 (IO1), J09.1 (PWR_A), U24.4 (OUT)
H09_PWR_B: D18.2 (IO2), J09.2 (PWR_B), U24.6 (OUT)
H09_RST_A: D19.1 (IO1), J09.3 (RST_A), U25.4 (OUT)
H09_RST_B: D19.2 (IO2), J09.4 (RST_B), U25.6 (OUT)
PHOTO_5V: R105.1, R109.1, R317.1, R318.1; also elsewhere on the board

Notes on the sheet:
Two isolated normally-open contacts parallel the original case buttons. No host LED sensing or isolated supply. Pin 9 remains this host reference for button ESD protection ONLY. Do not join host references to controller ground or to one another. Pins 5..8 and 10 are NC. Use verified motherboard sig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

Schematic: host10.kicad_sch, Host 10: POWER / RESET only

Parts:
D20, D21: PESD5V0S2BT; SOT-23; MPN PESD5V0S2BT; LCSC C2841440
D119, D120: KT-0603R / RED; LED_0603_1608Metric_CathodeSilk; MPN KT-0603R; LCSC C2286
J10: S10B-PHDSS(LF)(SN); JST_PHD_S10B-PHDSS_2x05_P2.00mm_Horizontal; MPN S10B-PHDSS(LF)(SN); LCSC C161672
Q23, Q24: MMBT3904; SOT-23; MPN MMBT3904(RANGE:100-300); LCSC C20526
R111, R115, R319, R320: 1.5k 1%; R_0603_1608Metric; MPN 0603WAF1501T5E; LCSC C22843
R112, R116: 100k 1%; R_0603_1608Metric; MPN 0603WAF1003T5E; LCSC C25803
R113, R114, R117, R118: 220 1%; R_0603_1608Metric; MPN 0603WAF2200T5E; LCSC C22962
U26, U27: TLP3122A(TPL,E; TLP3122A_11-4M1S; MPN TLP3122A(TPL,E; LCSC C4153843

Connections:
CTRL_H10_PWR_A: R114.2, U26.1 (A)
CTRL_H10_PWR_B: Q23.1 (B), R111.2, R112.1
CTRL_H10_PWR_IND_A: D119.2 (A), R319.2
CTRL_H10_PWR_K: D119.1 (K), Q23.3 (C), U26.3 (K)
CTRL_H10_PWR_R: R113.2, R114.1
CTRL_H10_RST_A: R118.2, U27.1 (A)
CTRL_H10_RST_B: Q24.1 (B), R115.2, R116.1
CTRL_H10_RST_IND_A: D120.2 (A), R320.2
CTRL_H10_RST_K: D120.1 (K), Q24.3 (C), U27.3 (K)
CTRL_H10_RST_R: R117.2, R118.1
DRV_19: R111.1; also elsewhere on the board
DRV_20: R115.1; also elsewhere on the board
GND_CTRL: Q23.2 (E), Q24.2 (E), R112.2, R116.2; also elsewhere on the board
H10_GND: D20.3 (GND), D21.3 (GND), J10.9 (HOST_REF)
H10_PWR_A: D20.1 (IO1), J10.1 (PWR_A), U26.4 (OUT)
H10_PWR_B: D20.2 (IO2), J10.2 (PWR_B), U26.6 (OUT)
H10_RST_A: D21.1 (IO1), J10.3 (RST_A), U27.4 (OUT)
H10_RST_B: D21.2 (IO2), J10.4 (RST_B), U27.6 (OUT)
PHOTO_5V: R113.1, R117.1, R319.1, R320.1; also elsewhere on the board

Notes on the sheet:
Two isolated normally-open contacts parallel the original case buttons. No host LED sensing or isolated supply. Pin 9 remains this host reference for button ESD protection ONLY. Do not join host references to controller ground or to one another. Pins 5..8 and 10 are NC. Use verified motherboard sig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

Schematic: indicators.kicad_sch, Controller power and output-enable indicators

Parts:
D201, D202: KT-0805G / GREEN; LED_0805_2012Metric_CathodeSilk; MPN KT-0805G; LCSC C2297
R321, R322: 330 1%; R_0603_1608Metric; MPN 0603WAF3300T5E; LCSC C23138

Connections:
3V3: R321.1, R322.1; also elsewhere on the board
EN_IND_A: D202.2 (A), R322.2
GND_CTRL: D201.1 (K); also elsewhere on the board
OUT_OE_N: D202.1 (K); also elsewhere on the board
PWR_IND_A: D201.2 (A), R321.2

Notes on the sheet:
PWR: 3V3 present. EN: OUT_OE_N low, output latches enabled. Per-host red PWR/RST indicators follow the photorelay driver AND PHOTO_5V. These indicate driver state, NOT actual contact closure or host power state. RJ45 built-in LINK/ACT LEDs retained. All indicators use controller ground.
